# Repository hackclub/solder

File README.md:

# solder

Solder is a beginner program where you make your first circuit board!! Plus, we'll give you a grant to order it + ship a kit components to you to assemble it :D

There is a tutorial to learn from scratch on the site. This program takes just around 5 hours to finish!

Start here: [solder.hackclub.com](https://solder.hackclub.com)

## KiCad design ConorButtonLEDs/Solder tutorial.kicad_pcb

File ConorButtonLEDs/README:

Schematic
Pictures wont upload to the README
Just followed the basic tutorial
 BOM
BT1	BatteryHolder_Keystone_3034_1x20mm	1	Battery_Cell
D1, D2	LED_D5.0mm	2	LED
R1, R2	R_Axial_DIN0207_L6.3mm_D2.5mm_P7.62mm_Horizontal	2	R

Slack username - @conor joyce

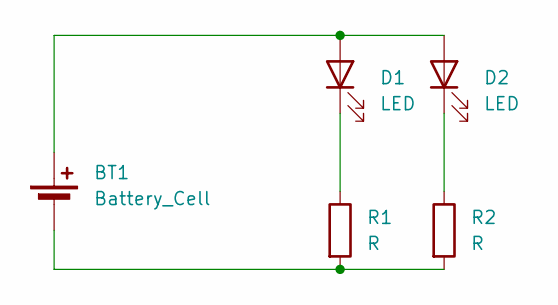
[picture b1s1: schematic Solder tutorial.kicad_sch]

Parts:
BT1: Battery_Cell; BatteryHolder_Keystone_3034_1x20mm
D1, D2: LED; LED_D5.0mm
R1, R2: R; R_Axial_DIN0207_L6.3mm_D2.5mm_P7.62mm_Horizontal

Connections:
unnamed: BT1.1 (+), D1.2 (A), D2.2 (A)
unnamed: BT1.2 (-), R1.2, R2.2
unnamed: D1.1 (K), R1.1
unnamed: D2.1 (K), R2.1

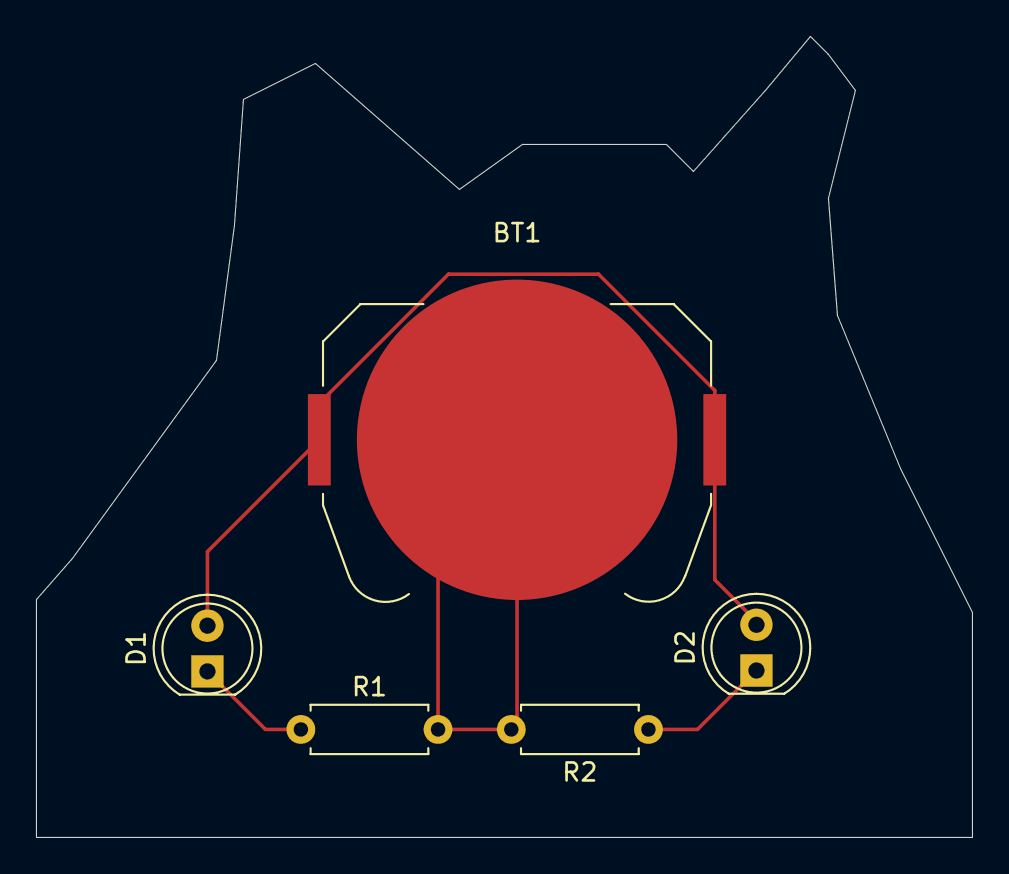
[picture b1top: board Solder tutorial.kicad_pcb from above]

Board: 2 copper layers, 52.0 x 44.5 mm, 5 parts (0 on the bottom side), 4 nets.

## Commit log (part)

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2025-03-21 Initial commit from Astro
2025-03-23 everything i got so far
2025-03-23 made the landing look decent
2025-03-23 main page content update
2025-03-23 Fix tutorial page's text's missing left padding
2025-03-23 Wow! I did so much!
2025-03-23 Start of the tutorial
2025-03-25 added kit contents!
2025-03-25 added pop effect on kit content cards
2025-03-25 Additions to tutorial
2025-03-25 Continue expanding tutorial
2025-03-26 Continue working on tutorial - Schematic part almost done
2025-03-26 More tutorial - part assignment
2025-03-27 change to main page
2025-03-27 changes to item list
2025-03-27 updated kit parts
2025-03-27 More parts
2025-03-27 Finished PCB tutorial
2025-03-27 Fix footprint
2025-03-27 Forgot about PNP transistors
2025-03-27 Add license and beautify guide
2025-03-27 Add text saying need to submit
2025-03-27 PR template
2025-03-27 update bom
2025-03-27 ton of style updates
2025-03-27 changed colors for visibility
2025-03-27 minor styling changes
2025-03-29 styling a little bit
2025-03-29 Markdown page rendering
2025-03-29 Automatic toc generation
2025-03-29 fix formatting on paragraph margins main page
2025-03-29 change paragraph margin css to only affect tutorial-page
2025-03-29 update styling
2025-03-29 Fix formatting
2025-03-30 Markdown sidebar + TOC
2025-03-30 Contents
2025-03-30 TOC on left side
2025-03-30 Animations
2025-03-30 update tutorial sidebar styling
2025-03-30 added logo to sidebar
2025-03-30 Change md files directory
2025-03-30 Fix animation
2025-03-30 Fix basic mobile layout
2025-03-30 tutorial styling
2025-03-30 sidebar styling changes
2025-03-30 update footer
2025-03-30 add shark
2025-03-30 Disable main animation on Chrome
2025-03-30 tutorial pages
2025-03-30 Markdown styling
2025-03-30 Corrected resistance formula in parallel circuits
2025-03-30 styling markdown
2025-03-31 update tutorial
2025-03-31 Change sidebar padding & margins
2025-03-31 Fix mobile layout
2025-03-31 update schematic of kicad tutorial
2025-03-31 update tutorial and submit flow
2025-04-01 really hope i didn't just break the landing formatting ahahaahhahahaha
2025-04-01 Change potentiometer footprint
2025-04-01 updates on submit flow
2025-04-01 slight copy changes
2025-04-01 update favicon
2025-04-02 slight updates
2025-04-02 center footer text
2025-04-02 Fix part highligiting
2025-04-02 Fix prod TOC
2025-04-02 Add some resources
2025-04-02 Fix mobile sidebar
2025-04-09 submition flow update
2025-04-09 copy edits
2025-04-11 Little tutorial on how to add graphics
2025-04-11 Add measure tool tip
2025-04-14 Sides, vias and gnd pour
2025-04-15 Add another resource
2025-04-15 Improve transistor description
2025-04-17 Improve the tutorial
2025-04-17 Onboard will probably end when solder starts :(
2025-04-19 Add info about THT and SMD, also add a few missing pictures
2025-04-22 Add how to add via hole
2025-04-22 Move keychain hole to advanced tutorial
2025-04-22 Fix capital letter missmatch
2025-04-22 feat: add dark mode to the docs
2025-04-22 chore: run prettier on everything
2025-04-22 feat: add theme toggle
2025-04-23 Default to light mode even when browser is in dark mode
2025-04-23 Also init to light mode
2025-04-23 Somehow the last commit didn't work
2025-04-23 Fix page switching resets to dark mode
2025-04-23 Add fix for invisible components
2025-04-23 Add part pictures
2025-04-24 EasyEDA Schematic Tutorial
2025-04-25 EasyEDA PCB
2025-04-26 emmit -> emit
2025-04-26 EasyEDA footprints
2025-04-29 Gate was for MOSFETS, it's called gate on transistors
2025-05-01 Add photo footprint
2025-05-04 Correct button naming
2025-05-04 Fix typo
2025-05-13 Fexed teh tppo
2025-05-16 add highway card to landing
2025-05-18 fixed dc motor footprint name
2025-05-20 Create just for the folder
2025-05-20 Create justforsrc
2025-08-20 remove highway card
2026-04-04 Bump defu from 6.1.4 to 6.1.6
    Bumps [defu](https://github.com/unjs/defu) from 6.1.4 to 6.1.6.
    - [Release notes](https://github.com/unjs/defu/releases)
    - [Changelog](https://github.com/unjs/defu/blob/main/CHANGELOG.md)
    - [Commits](https://github.com/unjs/defu/compare/v6.1.4...v6.1.6)
    ---
    updated-dependencies:
2026-04-07 Bump vite from 6.2.2 to 6.4.2
    Bumps [vite](https://github.com/vitejs/vite/tree/HEAD/packages/vite) from 6.2.2 to 6.4.2.
    - [Release notes](https://github.com/vitejs/vite/releases)
    - [Changelog](https://github.com/vitejs/vite/blob/v6.4.2/packages/vite/CHANGELOG.md)
    - [Commits](https://github.com/vitejs/vite/commits/v6.4.2/packages/vite)
    ---
    updated-dependencies:
2026-04-07 Bump picomatch
    Bumps and [picomatch](https://github.com/micromatch/picomatch). These dependencies needed to be updated together.
    Updates `picomatch` from 4.0.2 to 4.0.4
    - [Release notes](https://github.com/micromatch/picomatch/releases)
    - [Changelog](https://github.com/micromatch/picomatch/blob/master/CHANGELOG.md)
    - [Commits](https://github.com/micromatch/picomatch/compare/4.0.2...4.0.4)
    Updates `picomatch` from 2.3.1 to 2.3.2
2026-04-21 Bump astro from 5.5.4 to 6.1.6
    Bumps [astro](https://github.com/withastro/astro/tree/HEAD/packages/astro) from 5.5.4 to 6.1.6.
    - [Release notes](https://github.com/withastro/astro/releases)
    - [Changelog](https://github.com/withastro/astro/blob/main/packages/astro/CHANGELOG.md)
    - [Commits](https://github.com/withastro/astro/commits/astro@6.1.6/packages/astro)
    ---
    updated-dependencies:
2026-05-13 Bump astro from 5.5.4 to 6.1.10
    Bumps [astro](https://github.com/withastro/astro/tree/HEAD/packages/astro) from 5.5.4 to 6.1.10.
    - [Release notes](https://github.com/withastro/astro/releases)
    - [Changelog](https://github.com/withastro/astro/blob/main/packages/astro/CHANGELOG.md)
    - [Commits](https://github.com/withastro/astro/commits/astro@6.1.10/packages/astro)
    ---
    updated-dependencies:
